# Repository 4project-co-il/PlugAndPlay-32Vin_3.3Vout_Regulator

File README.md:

# PlugAndPlay: Regulator module for 32V IN, output: 3.3V/2A
This is the repository with the files for PlugAndPlay regulator module that accepts up to 32V input and output 3.3V/2A.

This module allows connecting higher voltages to the Plug-n-Play development boards.

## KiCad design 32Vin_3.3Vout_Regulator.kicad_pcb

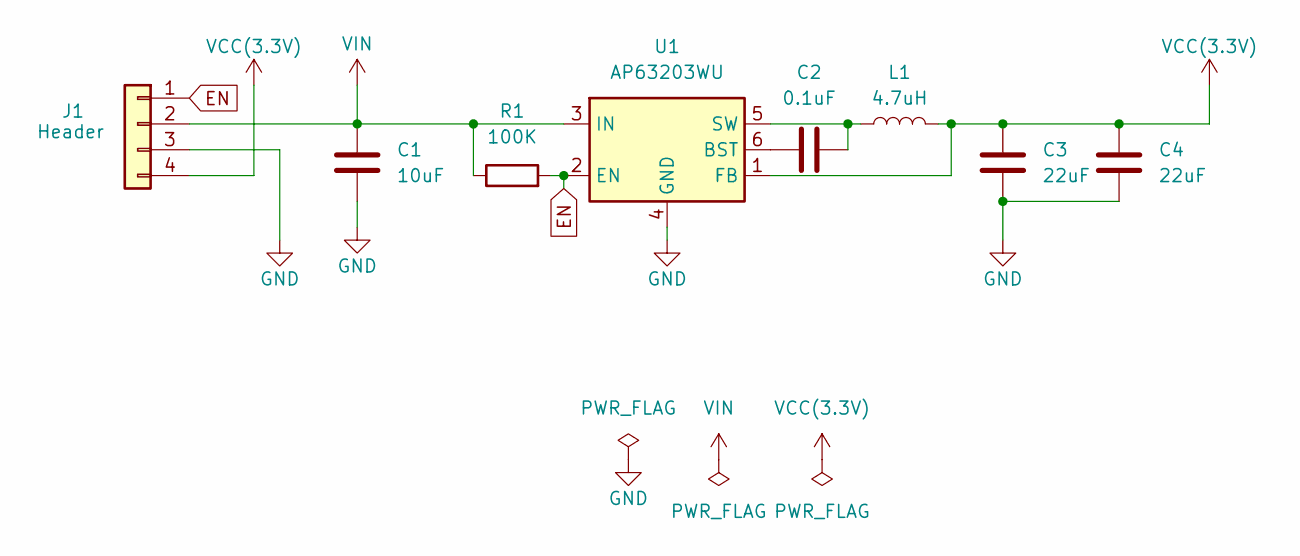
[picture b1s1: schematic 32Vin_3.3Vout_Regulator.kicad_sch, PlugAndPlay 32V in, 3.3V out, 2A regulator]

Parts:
C1: 10uF; C_1210_3225Metric
C2: 0.1uF; C_0603_1608Metric
C3, C4: 22uF; C_0603_1608Metric
J1: PinSocket_1x04_P2.54mm_Vertical_SMD_Pin1Left; MPN C780062
L1: 4.7uH; L_Chilisin_BMRA00040420
R1: 100K; R_0603_1608Metric
U1: AP63203WU; TSOT-23-6; MPN C780769

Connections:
EN: J1.1, R1.2, U1.2 (EN)
GND: C1.2, C3.2, C4.2, J1.3, U1.4 (GND)
unnamed: C2.1, U1.6 (BST)
unnamed: C2.2, L1.1, U1.5 (SW)
VCC(3.3V): C3.1, C4.1, J1.4, L1.2, U1.1 (FB)
VIN: C1.1, J1.2, R1.1, U1.3 (IN)

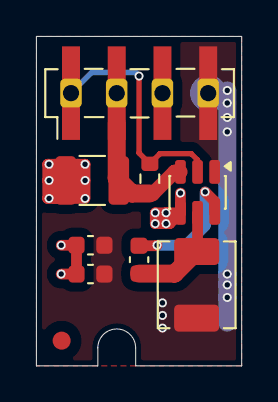
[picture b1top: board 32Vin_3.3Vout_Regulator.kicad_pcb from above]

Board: 2 copper layers, 11.4 x 18.3 mm, 8 parts (0 on the bottom side), 6 nets.

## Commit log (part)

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2025-12-15 MPN and feeder updated for the chip
